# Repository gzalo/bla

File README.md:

# BLA
Biblioteca liviana para Reconocimiento de Habla en español.

La idea es poder integrar de forma sencilla a una aplicación embebida ya existente el reconocimiento de palabras aisladas. Implementando únicamente lo mínimo requerido y de forma optimizada, se espera lograr tasas de errores muy bajas con consumo bajo de recursos.

Se incluye código de prueba para un microcontrolador de 32 bits LPC4337 (ARM Cortex M4/M0) como el de la Computadora Industrial Abierta Argentina (CIAA), en ejemplos/EDU-CIAA-baremetal.

[Documentación básica de la API](docs/API.md)

El proyecto fue desarrollado como trabajo final para la materia ["Seminario de Sistemas Embebidos"](http://laboratorios.fi.uba.ar/lse/seminario/) de la Facultad de Ingeniería de la UBA (FIUBA), en Buenos Aires, Argentina.

Detalles técnicos:

* Reconocimiento de palabras aisladas, independiente del hablante.
* La estrategia para detectar comienzo/fin de palabras se basa en una ventana deslizante, a la cual se le toma la energía. Dicha energía se compara con un umbral (con histéresis).
* El reconocimiento se basa en calcular los coeficientes MFCC de la señal capturada, y en base a los modelos ocultos de Markov, encontrar la palabra que es más probable que haya generado las observaciones.
* Los modelos de cada fonema están basados en varios estados que emiten mezclas de Gaussianas, con matrices de covarianza diagonales (internamente almacenada como sus inversas, para usar solo productos y no divisiones)
* Se corre el algoritmo de Viterbi por cada palabra, lo que encuentra la probabilidad del camino más probable. En base a esta probabilidad se ordenan las distintas palabras.
* Los cálculos de probabilidades se implementaron en espacios logarítmicos, para evitar problemas numéricos.
* La señal de audio debe estar muestreada a 16 KHz, de lo contrario es necesario reentrenar los modelos con otros datos de entrenamiento.	

Desarrollador: [Gonzalo Ávila Alterach / gzalo](http://gzalo.com)

---

Lightweight library for speech recognition.

The main idea is to integrate to an existing embedded application the ability to recognise isolated words. By implementing just the needed modules, and optimizing the code, low error rate with low resource usage is expected.

Test code for a 32 bits LPC4337 microcontroller (ARM Cortex M4/M0) like the one from the Computadora Industrial Abierta Argentina (CIAA) is included, in the folder ejemplos/EDU-CIAA-baremetal.

[Basic API Documentation (in spanish)](docs/API.md)

This project was developed for the assignature ["Seminario de Sistemas Embebidos"](http://laboratorios.fi.uba.ar/lse/seminario/) of UBA Faculty of Engineering (FIUBA), in Buenos Aires, Argentina.

Specifications:

* Speaker independent, Isolated word recognition.
* Voice activity detection based in energy of a sliding window, which is compared to a threshold (with some histeresis).
* Recognition based in MFCC coefficients, and Hidden Markov Models. The most likely N-words are displayed.
* Per phoneme models, based on Gaussian mixtures, with diagonal covariance matrices.
* Viterbi algorithm is executed once for each word, which finds the probability of the most probable path. Words are sorted by their probability.
* Log-spaces are used to calculate probabilities and to use Viterbi, in order to avoid numerical problems.
* Audio input signal must be sampled at 16 KHz (or a higher rate and downsampled via decimation or averaging, check sample code), otherwise the models must be replaced with others which must be trained with the correct sample rate.

Developer: [Gonzalo Ávila Alterach / gzalo](http://gzalo.com)

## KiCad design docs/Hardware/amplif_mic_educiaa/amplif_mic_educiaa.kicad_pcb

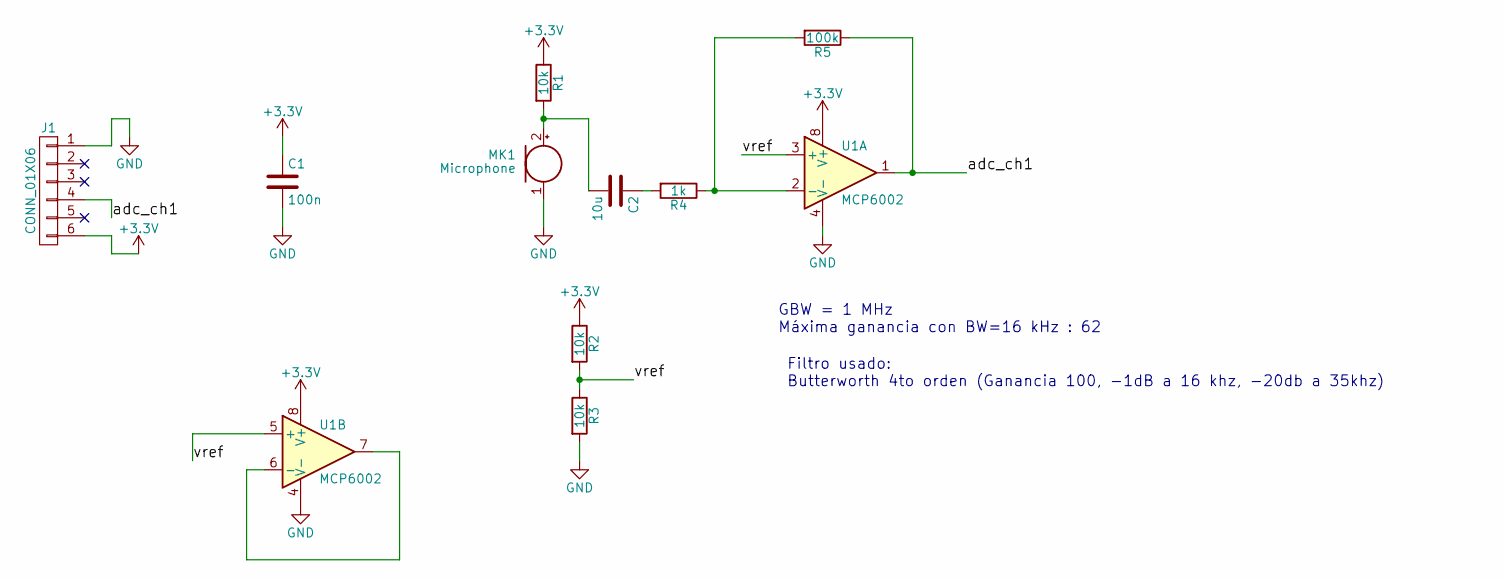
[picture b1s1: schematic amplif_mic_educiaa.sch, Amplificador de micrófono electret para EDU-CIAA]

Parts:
C1: 100n; C_0805_HandSoldering
C2: 10u; C_0805_HandSoldering
J1: CONN_01X06; Pin_Header_Straight_1x06_Pitch2.54mm
MK1: Microphone; Pin_Header_Straight_1x02_Pitch2.54mm
R1, R2, R3: 10k; R_0805_HandSoldering
R4: 1k; R_0805_HandSoldering
R5: 100k; R_0805_HandSoldering
U1: MCP6002; DIP-8_W7.62mm

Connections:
+3V3: C1.1, J1.6, R1.1, R2.1, U1.8 (V+)
/adc_ch1: J1.4, R5.1, U1.1
/vref: R2.2, R3.1, U1.3 (+), U1.5 (+)
GND: C1.2, J1.1, MK1.1 (-), R3.2, U1.4 (V-)
unnamed: C2.1, R4.2
unnamed: C2.2, MK1.2 (+), R1.2
unnamed: R4.1, R5.2, U1.2 (-)
unnamed: U1.6 (-), U1.7

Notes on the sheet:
GBW = 1 MHz Máxima ganancia con BW=16 kHz : 62
Filtro usado: Butterworth 4to orden (Ganancia 100, -1dB a 16 khz, -20db a 35khz)

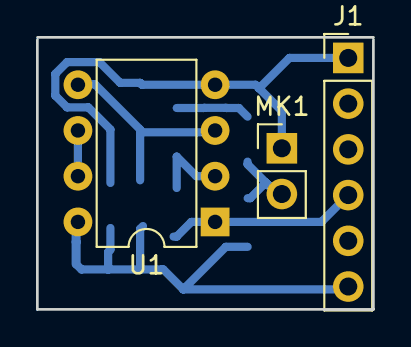
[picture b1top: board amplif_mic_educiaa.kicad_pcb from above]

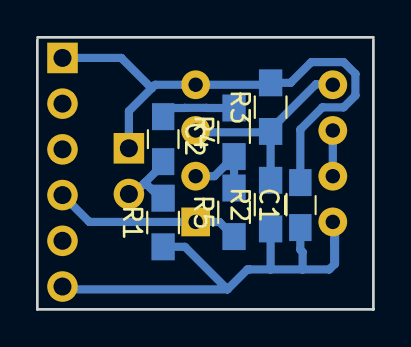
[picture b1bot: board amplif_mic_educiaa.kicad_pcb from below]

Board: 2 copper layers, 18.7 x 15.1 mm, 10 parts (7 on the bottom side), 8 nets.

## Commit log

2016-11-01 Agregado readme más completo
2016-12-03 Primer commit público
2016-12-04 Agregado de documentación de API
    Agregado de chequeo de largo (si cantidadLista era mayor a la cantidad
    de palabras, leía de cualquier lado)
2016-12-04 Arreglo de link incorrecto y mejora de formato
2016-12-04 Resumen de tests/generadores
2016-12-13 Readme en inglés y cambios menores
2017-06-07 Agregado esquema y PCB nuevo amplificador de mic
2019-08-23 Created empty lib folder to avoid error when compiling, added programming of bank B of flash memory
